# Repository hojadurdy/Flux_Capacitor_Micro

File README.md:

# Flux Capacitor Micro

### WHAT IS IT?

A tiny (36mm x 29mm) pin badge and keychain PCB version of Flux Capacitor featuring 25 animated LEDs that animate to create the “fluxxing” effect. It’s 100% decorative, it doesn’t actually let you travel through time when worn around the neck.

This tiny Flux Capacitor is controlled by a Microchip ATtiny1616 microcontroller. Thankfully this board has a much lower power requirement than the silkscreen indicates on the back, and skips along, sipping power from the single CR2016/LIR2016 coin cell battery (instead of plutonium or a lightning strike), slipped into the rear mounted coin cell holder. By using PWM (Pulse Width Modulation) pins for 8 channels of 3 paralleled LEDs, different animation patterns are generated for the fluxxxing effect. In settings mode, users are able change between 8 different animation, speed and LED brightness.

### WHAT IS NEW WITH THIS DESIGN?

- Main difference is the new design significantly slimmer due to slim battery holder and changing PCB thickness from 1.6mm to 0.8mm. Older design (V3) had a thickness of 6.15mm, the new design is only 3.4mm thick. 
- Front design has been updated to look like similar to Flux Capacitor Mini design. 
- A much brighter center LED has been added to get a brighter center beam flash, similar to the original Flux Capacitor.
- Instead of just 2 animations, now there are 8 different animations that can be selected in settings.
- Power toggle switch has been replaced with a push button. When pressed device goes in do "Power Down" mode. during "Power Down" mode device only consumes 0.5 uA.

Below you can see the thickness comparison of V3 on the left and V4 on the right.

### HOW LONG WILL THE BATTERY LAST?

CR2016 (Non-Rechargeable) with average of 90 mAh battery capacity.

- 100% LED Brightness :  80 Hours
- 25%  LED Brightness :  128 Hours

LIR2016 (Rechargeable) with average of 20 mAh battery capacity.

- 100% LED Brightness :  18 Hours
- 25%  LED Brightness :  28 Hours

### HOW TO SETUP AND OPERATE

To begin with, turn on the device by pressing power button. In order to enter settings mode just hold the set button for 1 second. If all of the LEDs flashes twice, you are successfully entered settings mode. 

After the LEDs flash you will see that only single LED remains on. That single LED shows which animation is selected. To change that, just short press the set button and the LED should start shifting from inner to outer LED with each press. After selecting the preferred animation, hold the set button for 1 second to save. LEDs should flash twice to confirm.

Next setting is animation speed. To change the animation speed, just short press the set button to increase the speed. LEDs will turn on from inner to outer to indicate animation speed. At maximum speed all LEDs should be on. Hold the set button for 1 second to save animation speed. LEDs should flash twice to confirm.

Last setting is LED brightness. Same as before to change the brightness just short press the set buttonto increase the brightness. LEDs will turn on from inner to outer to indicate brightness level. At maximum brightness all LEDs should be on. Hold the set button for 1 second to save brightness setting. LEDs should flash twice to confirm and device should exit the setting mode. LEDs should start animating.

**If you short press the button with gear icon during normal operation, device initiates engage mode.
LEDs start to animate faster with much brighter center beam as shown in the video below.**

### P.S.
**Only CR2016 or LIR2016 batteries are compatible. If you prefer to use larger CR2032 or LIR2032 batteries, message me from store page. I will change the battery holder to a larger one. Also batteries are not included due to shipping restrictions.**

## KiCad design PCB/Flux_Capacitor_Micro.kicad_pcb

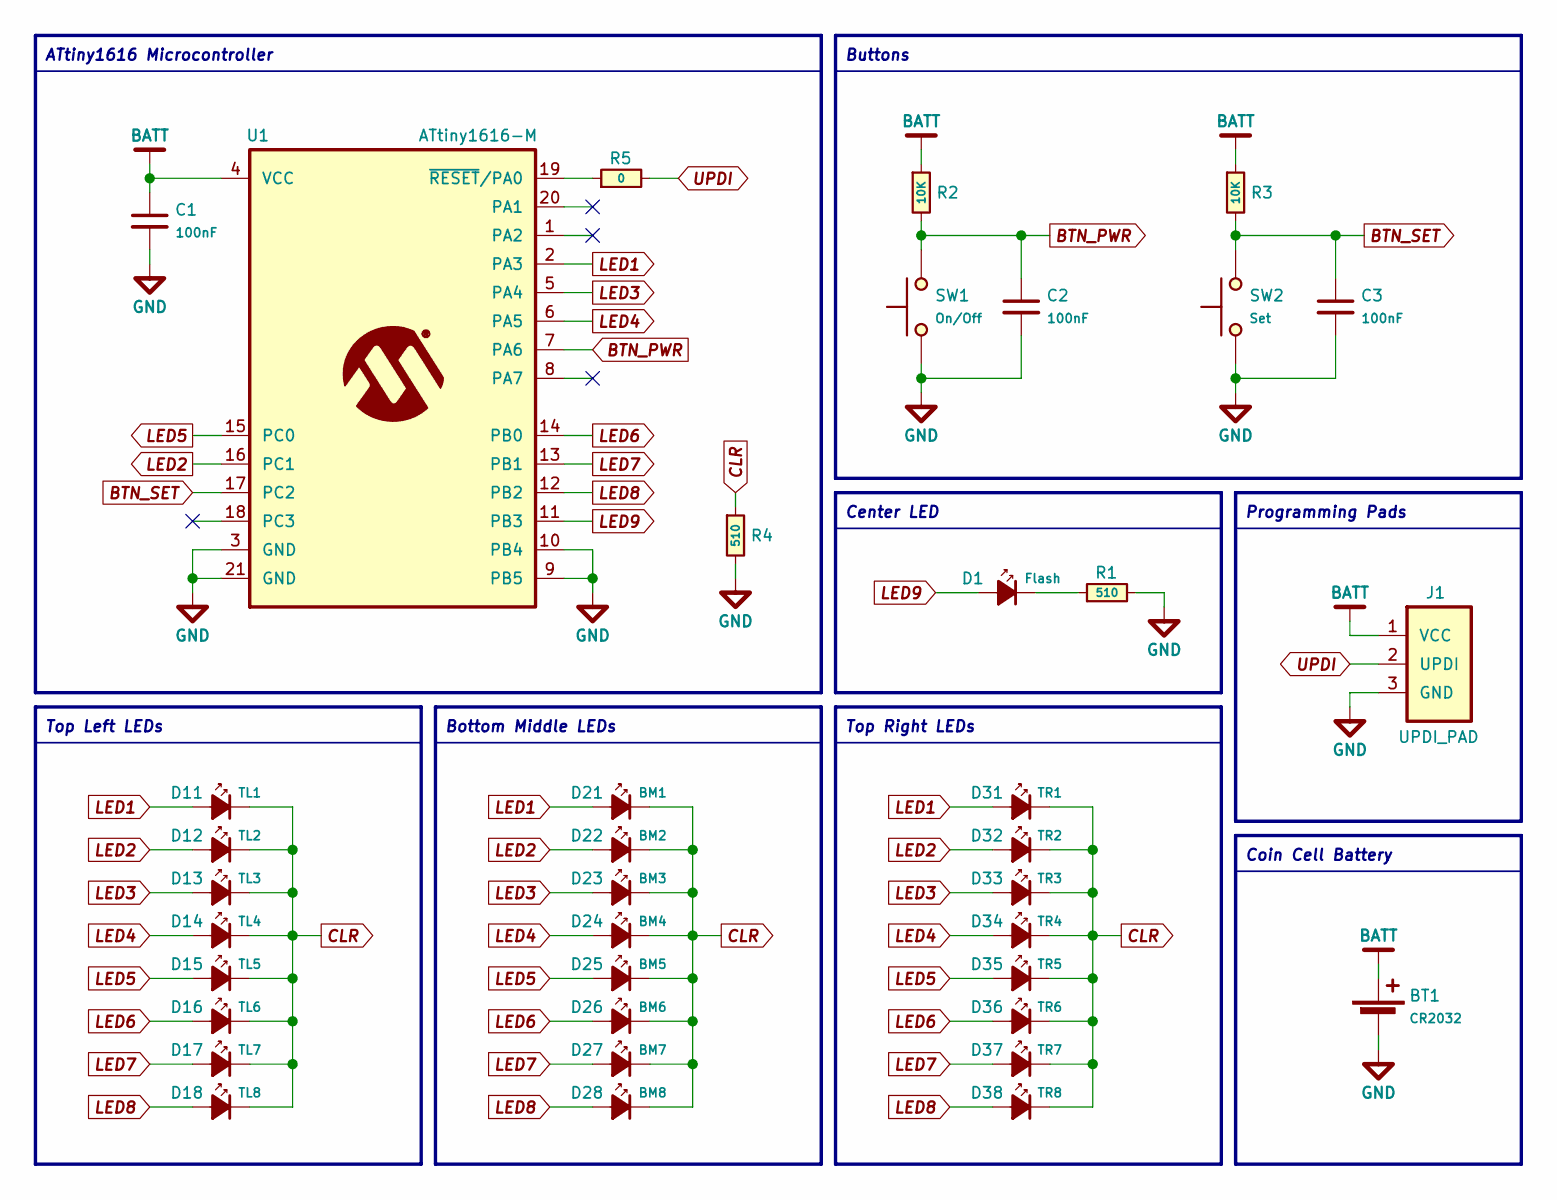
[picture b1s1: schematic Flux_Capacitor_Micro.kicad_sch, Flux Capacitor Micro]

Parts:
BT1: CR2032; MY-2016-02
C1, C2, C3: 100nF; C_0402_1005Metric
D1: Flash; LED_0402_1005Metric
D11: TL1; LED_0402_1005Metric
D12: TL2; LED_0402_1005Metric
D13: TL3; LED_0402_1005Metric
D14: TL4; LED_0402_1005Metric
D15: TL5; LED_0402_1005Metric
D16: TL6; LED_0402_1005Metric
D17: TL7; LED_0402_1005Metric
D18: TL8; LED_0402_1005Metric
D21: BM1; LED_0402_1005Metric
D22: BM2; LED_0402_1005Metric
D23: BM3; LED_0402_1005Metric
D24: BM4; LED_0402_1005Metric
D25: BM5; LED_0402_1005Metric
D26: BM6; LED_0402_1005Metric
D27: BM7; LED_0402_1005Metric
D28: BM8; LED_0402_1005Metric
D31: TR1; LED_0402_1005Metric
D32: TR2; LED_0402_1005Metric
D33: TR3; LED_0402_1005Metric
D34: TR4; LED_0402_1005Metric
D35: TR5; LED_0402_1005Metric
D36: TR6; LED_0402_1005Metric
D37: TR7; LED_0402_1005Metric
D38: TR8; LED_0402_1005Metric
J1: UPDI_PAD; PogoPad_1x03_P1.27mm
R1, R4: 510; R_0402_1005Metric
R2, R3: 10K; R_0402_1005Metric
R5: 0; R_0402_1005Metric
SW1: On/Off; K2-1809SN-D4DW-06
SW2: Set; K2-1809SN-D4DW-06
U1: ATtiny1616-M; VQFN-20-1EP_3x3mm_P0.4mm_EP1.7x1.7mm

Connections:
BATT: BT1.1 (+), C1.1, J1.1 (VCC), R2.1, R3.1, U1.4 (VCC)
BTN_PWR: C2.1, R2.2, SW1.2, U1.7 (PA6)
BTN_SET: C3.1, R3.2, SW2.2, U1.17 (PC2)
CLR: D11.1 (K), D12.1 (K), D13.1 (K), D14.1 (K), D15.1 (K), D16.1 (K), D17.1 (K), D18.1 (K), D21.1 (K), D22.1 (K), D23.1 (K), D24.1 (K), D25.1 (K), D26.1 (K), D27.1 (K), D28.1 (K), D31.1 (K), D32.1 (K), D33.1 (K), D34.1 (K), D35.1 (K), D36.1 (K), D37.1 (K), D38.1 (K), R4.1
GND: BT1.2 (-), C1.2, C2.2, C3.2, J1.3 (GND), R1.2, R4.2, SW1.1, SW2.1, U1.3 (GND), U1.9 (PB5), U1.10 (PB4), U1.21 (GND)
LED1: D11.2 (A), D21.2 (A), D31.2 (A), U1.2 (PA3)
LED2: D12.2 (A), D22.2 (A), D32.2 (A), U1.16 (PC1)
LED3: D13.2 (A), D23.2 (A), D33.2 (A), U1.5 (PA4)
LED4: D14.2 (A), D24.2 (A), D34.2 (A), U1.6 (PA5)
LED5: D15.2 (A), D25.2 (A), D35.2 (A), U1.15 (PC0)
LED6: D16.2 (A), D26.2 (A), D36.2 (A), U1.14 (PB0)
LED7: D17.2 (A), D27.2 (A), D37.2 (A), U1.13 (PB1)
LED8: D18.2 (A), D28.2 (A), D38.2 (A), U1.12 (PB2)
LED9: D1.2 (A), U1.11 (PB3)
unnamed: D1.1 (K), R1.1
unnamed: R5.1, U1.19 (~RESET/PA0)
UPDI: J1.2 (UPDI), R5.2

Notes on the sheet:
Coin Cell Battery
Center LED
Top Right LEDs
Bottom Middle LEDs
Top Left LEDs
Programming Pads
ATtiny1616 Microcontroller
Buttons

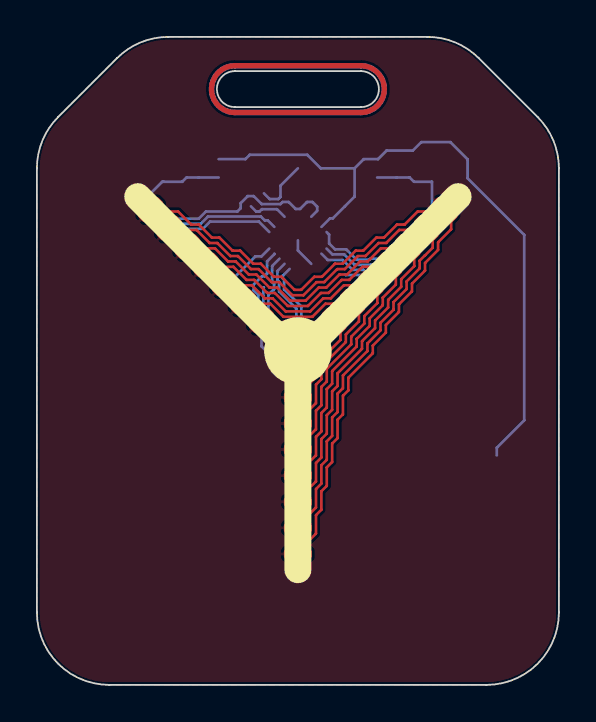
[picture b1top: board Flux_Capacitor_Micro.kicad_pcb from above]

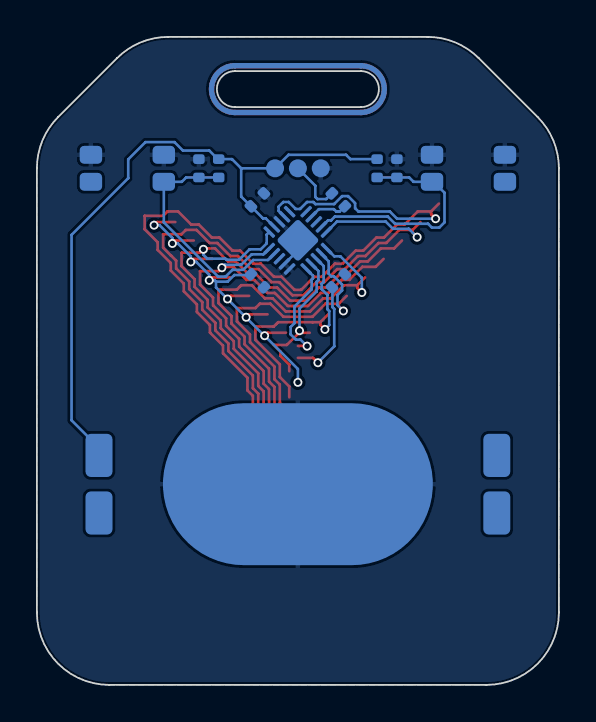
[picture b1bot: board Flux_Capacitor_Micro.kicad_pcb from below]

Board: 2 copper layers, 29.0 x 36.0 mm, 40 parts (14 on the bottom side), 17 nets.

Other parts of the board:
svg2mod, svg2mod#2: G***; svg2mod

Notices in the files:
PCB/Flux_Capacitor_Micro.kicad_pcb:
CC BY-NC-SA 4.0
